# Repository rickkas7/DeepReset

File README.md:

# Deep Reset Tutorial

This tutorial is a simple example of how to use the EN pin on the Argon/Boron/Xenon to power down the device for around 30 seconds. 

Say you have a Boron in a remote location. The device knows it's having trouble connecting to the cloud. Maybe power cycling it would help. This simple circuit powers off both the modem and the nRF52 MCU using an external timer. Pulling the EN line low turns off the load switch powering the modem and the nRF52 MCU on the Boron.

On the Argon and Xenon it powers off the XCL223 3.3V regulator, which will de-power the nRF52 MCU and on the Argon, the ESP32.

After about 30 seconds, the device will be allowed to boot normally.

Updates and the associated files can be found here:
[https://github.com/rickkas7/DeepReset](https://github.com/rickkas7/DeepReset)

## Test Board

This is the test board for this circuit. While you can build this board exactly as is, you'll typically want to include the circuit on your own board rather than dedicate an entire FeatherWing to resetting.

Schematics:

Board layout:

By default D2 is the deep reset pin, but you can change that using the configuration jumper pads on the bottom of the board.

If you set D2 to OUTPUT and make it go HIGH, the device will immediately power down for around 30 seconds, then essentially cold boot. The MCU and modem will be de-powered during this time using the EN pin.

You can tell it's working because the device turns off, the EN pin goes LOW, and 3V3 will become unpowered during this deep reset de-powered phase.

### Eagle directory

The eagle directory in this repository contains:

- DeepReset2.sch - schematic
- DeepReset2.brd - board layout
- DeepReset2v1.zip - Gerbers
- DeepReset2.lbr - library containing all of the components in this design

### BOM

| Quantity | Item | Example |
| --- | --- | --- |
| 2 | 10K resistor 0603 | [Panasonic ERJ-PA3J103V](https://www.digikey.com/product-detail/en/panasonic-electronic-components/ERJ-PA3J103V/P10KBZCT-ND/503623) |
| 1 | 100K resistor 0603 | [Panasonic ERJ-3EKF1003V](https://www.digikey.com/product-detail/en/panasonic-electronic-components/ERJ-3EKF1003V/P100KHCT-ND/198110) |
| 1 | 2.7M resistor 0603 | [Panasonic ERJ-3GEYJ275V](https://www.digikey.com/product-detail/en/panasonic-electronic-components/ERJ-3GEYJ275V/P2.7MGCT-ND/282431) | 
| 1 | 0.01uF capacitor 0603 | [Murata GCM188R72A103KA37J](https://www.digikey.com/product-detail/en/murata-electronics-north-america/GCM188R72A103KA37J/490-8028-1-ND/4380313) |
| 1 | 10uF capacitor 0805 | [Murata GRM21BR61C106KE15L](https://www.digikey.com/product-detail/en/murata-electronics-north-america/GRM21BR61C106KE15L/490-3886-1-ND/965928) | 
| 2 | RS1JFP diode | [ON Semiconductor RS1JFP](https://www.digikey.com/product-detail/en/on-semiconductor/RS1JFP/RS1JFPCT-ND/5722970) |
| 2 | 2N7002 N-MOSFET | [ON Semiconductor 2N7002LT3G](https://www.digikey.com/product-detail/en/on-semiconductor/2N7002LT3G/2N7002LT3GOSCT-ND/2704932) |
| 1 | TS555 Timer | [ST Microelectronics TS555](https://www.digikey.com/product-detail/en/stmicroelectronics/TS555IDTTR/497-16404-1-ND/5959811) | 
| 1 | RT9818 Voltage Detector | [Richtek RT9818C-29GV](https://www.digikey.com/product-detail/en/richtek-usa-inc/RT9818C-29GV/1028-1020-1-ND/2470079) |
| | Male header pins 0.1" | [Sullins PRPC040SAAN-RC](https://www.digikey.com/product-detail/en/PRPC040SAAN-RC/S1011EC-40-ND/2775214) |

## Firmware

This is the test firmware. When you hit the MODE button, the device should immediately go into deep reset for 30 or so seconds.

```
#include "Particle.h"

SYSTEM_THREAD(ENABLED);

SerialLogHandler logHandler;

const int DEEP_RESET_PIN = D2;

void buttonHandler();

void setup() {
	pinResetFast(DEEP_RESET_PIN);
	pinMode(DEEP_RESET_PIN, OUTPUT);

	System.on(button_click, buttonHandler);
}

void loop() {

}

void buttonHandler() {
	Log.info("about to deep reset");

	digitalWrite(DEEP_RESET_PIN, HIGH);

	delay(1000);
	Log.info("this should never be reached");
}

```

The setup code look like this:

```
pinResetFast(DEEP_RESET_PIN);
pinMode(DEEP_RESET_PIN, OUTPUT);
```

Note the use of pinResetFast. This is necessary because digitalWrite does not work before the pin is set to output. Since the default state of outputs is LOW the pinResetFast shouldn't be necessary, but I added it to be safe. This makes sure the pin won't go briefly high, which will cause the device to go to deep reset immediately.

## Configuration Pads

On the bottom side of the board are a number of trace jumpers that configure which pin is the deep reset pin. The default is D2.

To change it, cut the trace on the D2 pads, highlighted here:

Then close one of the other trace jumpers on D3, D4, A0, A1, or A2. A little blob of solder should do it. And, if you want to change it again, you can just vacuum or solder wick the blob off and move it to another pad.

## Circuit Deep Dive

These two RS1JFP diodes allow the board to be powered either by USB or battery for flexibility. It you will only be powered by one or the other you can just skip the diodes, but if you could be powered with either than you'll need the diodes.

One pin is used to enter deep reset by setting the pin as OUTPUT and setting it HIGH. This circuit is necessary for a few reasons:

- The TS555 Timer requires an active low trigger.
- The DRST line connects to the TS555 timer TRIGGER line with a pull-up to PWR, which can be up to 4.9V when powered by USB. Connecting GPIO directly to DRST would damage the GPIO.
- The 2N7002 N-channel MOSFET prevents this higher voltage from flowing backwards into the GPIO pin and also inverts the signal.

The state of the timer at power-up cannot be guaranteed. To make sure that the device immediately starts when powered on, a Richtek RT9818 power detector is connected to the RESET pin on the TS555 timer. There's a 100K weak pull-up on the pin as the RT9818 is an open-collector active-low output. The RT9818 is $0.41 in single quantities. 

You can omit it, however sometimes the device will then go into deep reset at power-up. It will recover after 30 seconds, but it's disconcerting when it happens so I like to include the RT9818.

This circuit is from the datasheet and describes using a 555 timer in monostable (one-shot) mode.

The control voltage capacitor is always 0.01µF. The configurable part is R and C.

The actual circuit has:

- R is 2.7 MΩ
- C is 10µF

The timing formula for monostable operation is:

- 1.1 &times; R &times; C

Where:

- R is in ohms
- C is in Farads

So:

- 1.1 &times; 2.7E<sup>6</sup> &times; 10E<sup>-6</sup> = 29.7 seconds 

[This page](https://www.electronics-tutorials.ws/waveforms/555_timer.html) has a great introduction to the various modes of the 555 timer.

By the way, this particular circuit uses the ST Microelectronics TS555. The classic bipolar 555 timer requires a minimum of 4.5V and 20 mA to do its thing. The TS555 works from 2V to 16V at around 100 µA, making it much better suited for battery-powered applications.

Finally, the output circuit uses a 2N7002 N-channel MOSFET. The timer output is active high, and the MOSFET pull the EN line low when the timer output goes high. The EN line has a 100K weak pull-up on it on the device itself, so this works perfectly.

Also, the TS555 timer can be running at 4.9V when powered by USB. We don't want to drive the EN line with that high of a voltage, so using the N-channel MOSFET in open-collector style is preferable.

## Warning

Make sure you don't have any GPIO connected to voltages other than 3V3, such as a with a pull-up to a different supply, or a circuit that could back-feed the GPIO. If you have power leaking into GPIO when the EN pin is held low, it's possible that this leakage current will keep the nRF52 powered up, and it won't reset by pulling the EN line low.

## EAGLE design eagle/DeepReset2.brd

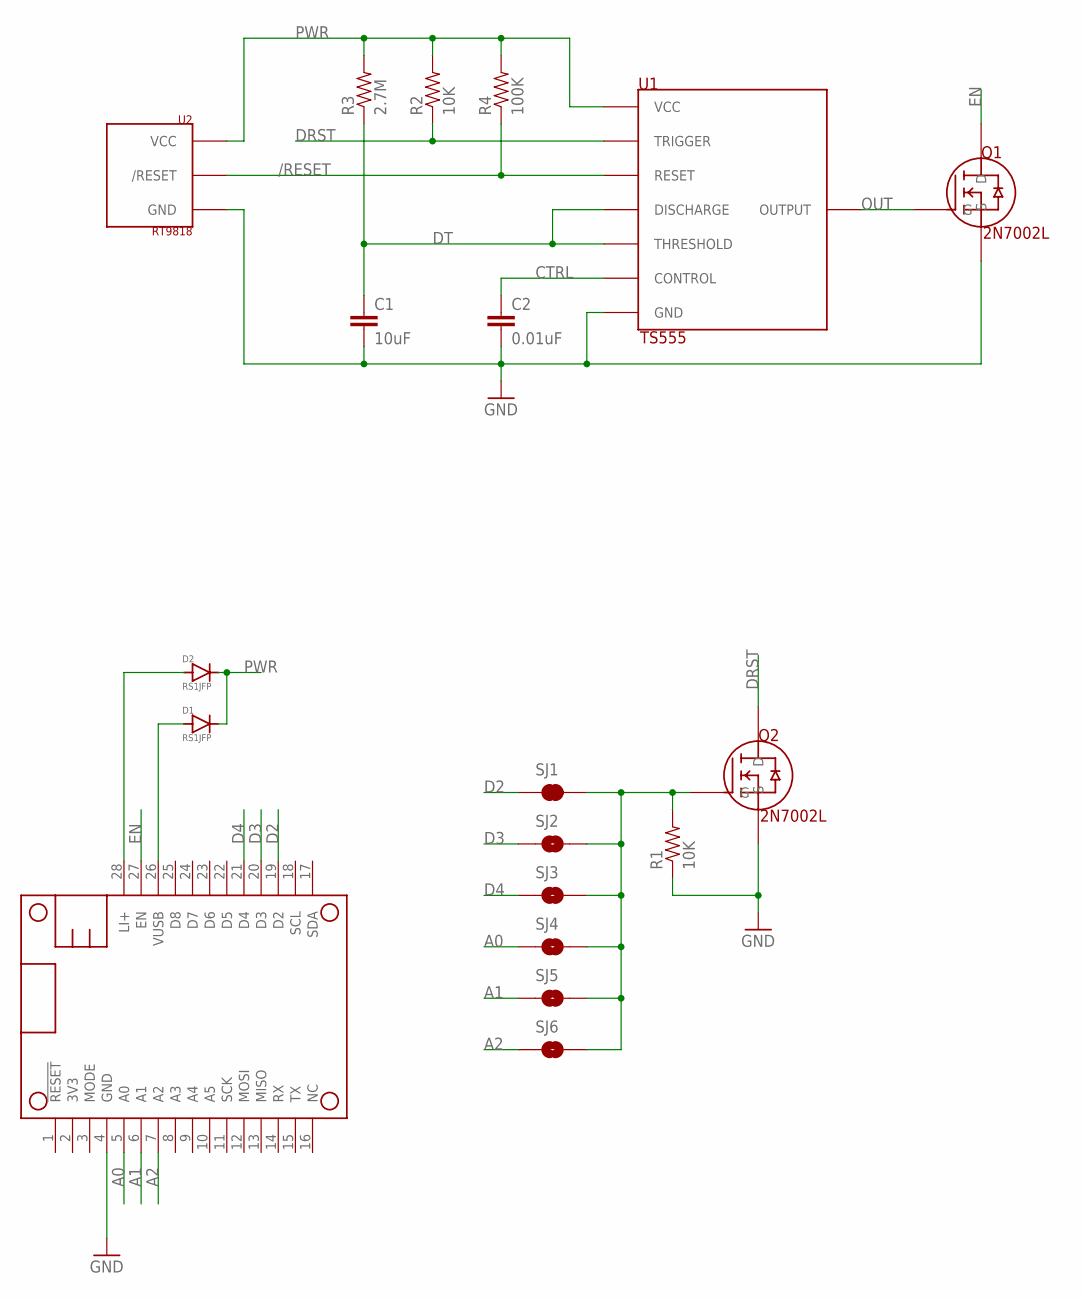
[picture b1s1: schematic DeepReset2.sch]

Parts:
C1: 10uF; 0603-CAP
C2: 0.01uF; 0603-CAP
D1, D2: RS1JFP; SOD-123HE-ON
MS1: FEATHERWING_NODIM
Q1, Q2: 2N7002L
R1, R2: 10K; 0603-RES
R3: 2.7M; 0603-RES
R4: 100K; 0603-RES
SJ1: JUMPER-PAD-2-NC_BY_TRACENO_SILK; PAD-JUMPER-2-NC_BY_TRACE_NO_SILK
SJ2, SJ3, SJ4, SJ5, SJ6: JUMPER-PAD-2-NO; PAD-JUMPER-2-NO_NO_SILK
U1: TS555; 8-SOIC-MICROCHIP-3.9
U2: RT9818; SOT-23-3

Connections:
/RESET: R4.1, U1.4 (RESET), U2.1 (/RESET)
A0: MS1.5 (A0), SJ4.1
A1: MS1.6 (A1), SJ5.1
A2: MS1.7 (A2), SJ6.1
AD: Q2.1 (G), R1.2, SJ1.2, SJ2.2, SJ3.2, SJ4.2, SJ5.2, SJ6.2
CTRL: C2.1, U1.5 (CONTROL)
D2: MS1.19 (D2), SJ1.1
D3: MS1.20 (D3), SJ2.1
D4: MS1.21 (D4), SJ3.1
DRST: Q2.3 (D), R2.1, U1.2 (TRIGGER)
DT: C1.1, R3.1, U1.6 (THRESHOLD), U1.7 (DISCHARGE)
EN: MS1.27 (EN), Q1.3 (D)
GND: C1.2, C2.2, MS1.4 (GND), Q1.2 (S), Q2.2 (S), R1.1, U1.1 (GND), U2.2 (GND)
LI+: D2.2 (ANODE), MS1.28 (LI+)
OUT: Q1.1 (G), U1.3 (OUTPUT)
PWR: D1.1 (CATHODE), D2.1 (CATHODE), R2.2, R3.2, R4.2, U1.8 (VCC), U2.3 (VCC)
VUSB: D1.2 (ANODE), MS1.26 (VUSB)

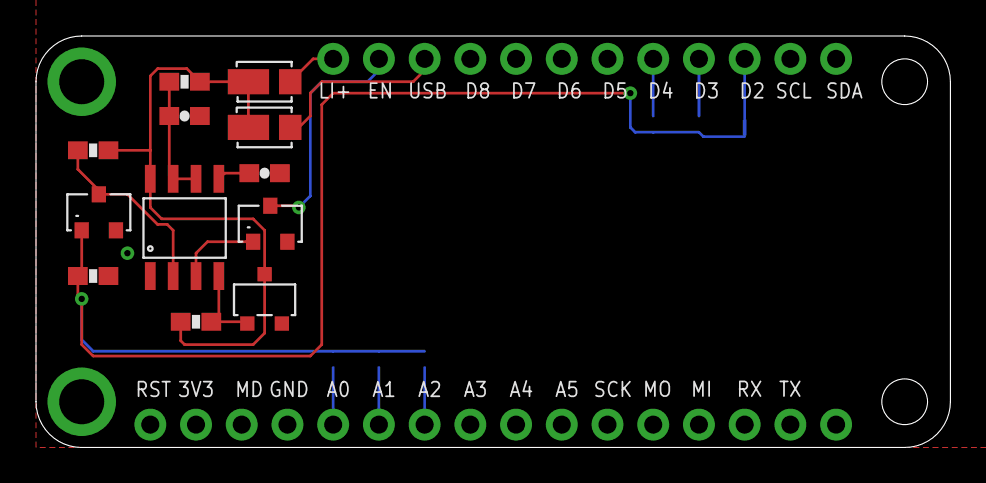
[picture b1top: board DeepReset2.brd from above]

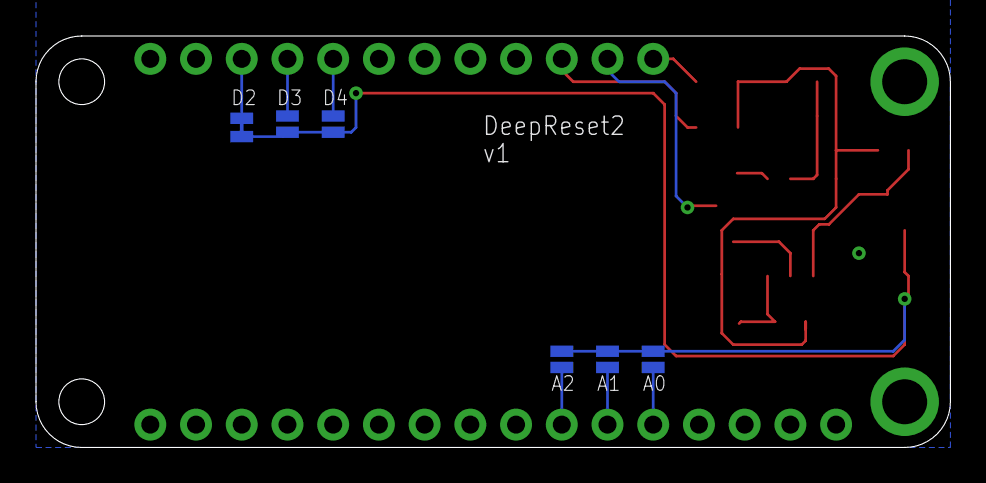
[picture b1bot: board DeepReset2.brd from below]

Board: 2 copper layers, 50.8 x 22.9 mm, 19 parts (6 on the bottom side), 17 nets.

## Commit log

2019-08-09 Initial version
2019-08-09 Fix voltage for bipolar 555
2019-08-12 Minor text edits
2020-08-10 Add warning
